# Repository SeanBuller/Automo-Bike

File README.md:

## Automo-Bike

Automatic bicycle gear changer (transmission). Fourth year design project (Capstone) for ECE (Electrical & Computer Engineering) at University of Waterloo.

## Synopsis

Controls 2 stepper motors based on external inputs from hall-effect sensor, and IMU (inertial measurement unit). 12 V battery input with 5 V regulator for MCU. 

The design is intended to be paired with the following stepper motors: 17HS13-0404S-PG27 and SY20STH30-0604A.

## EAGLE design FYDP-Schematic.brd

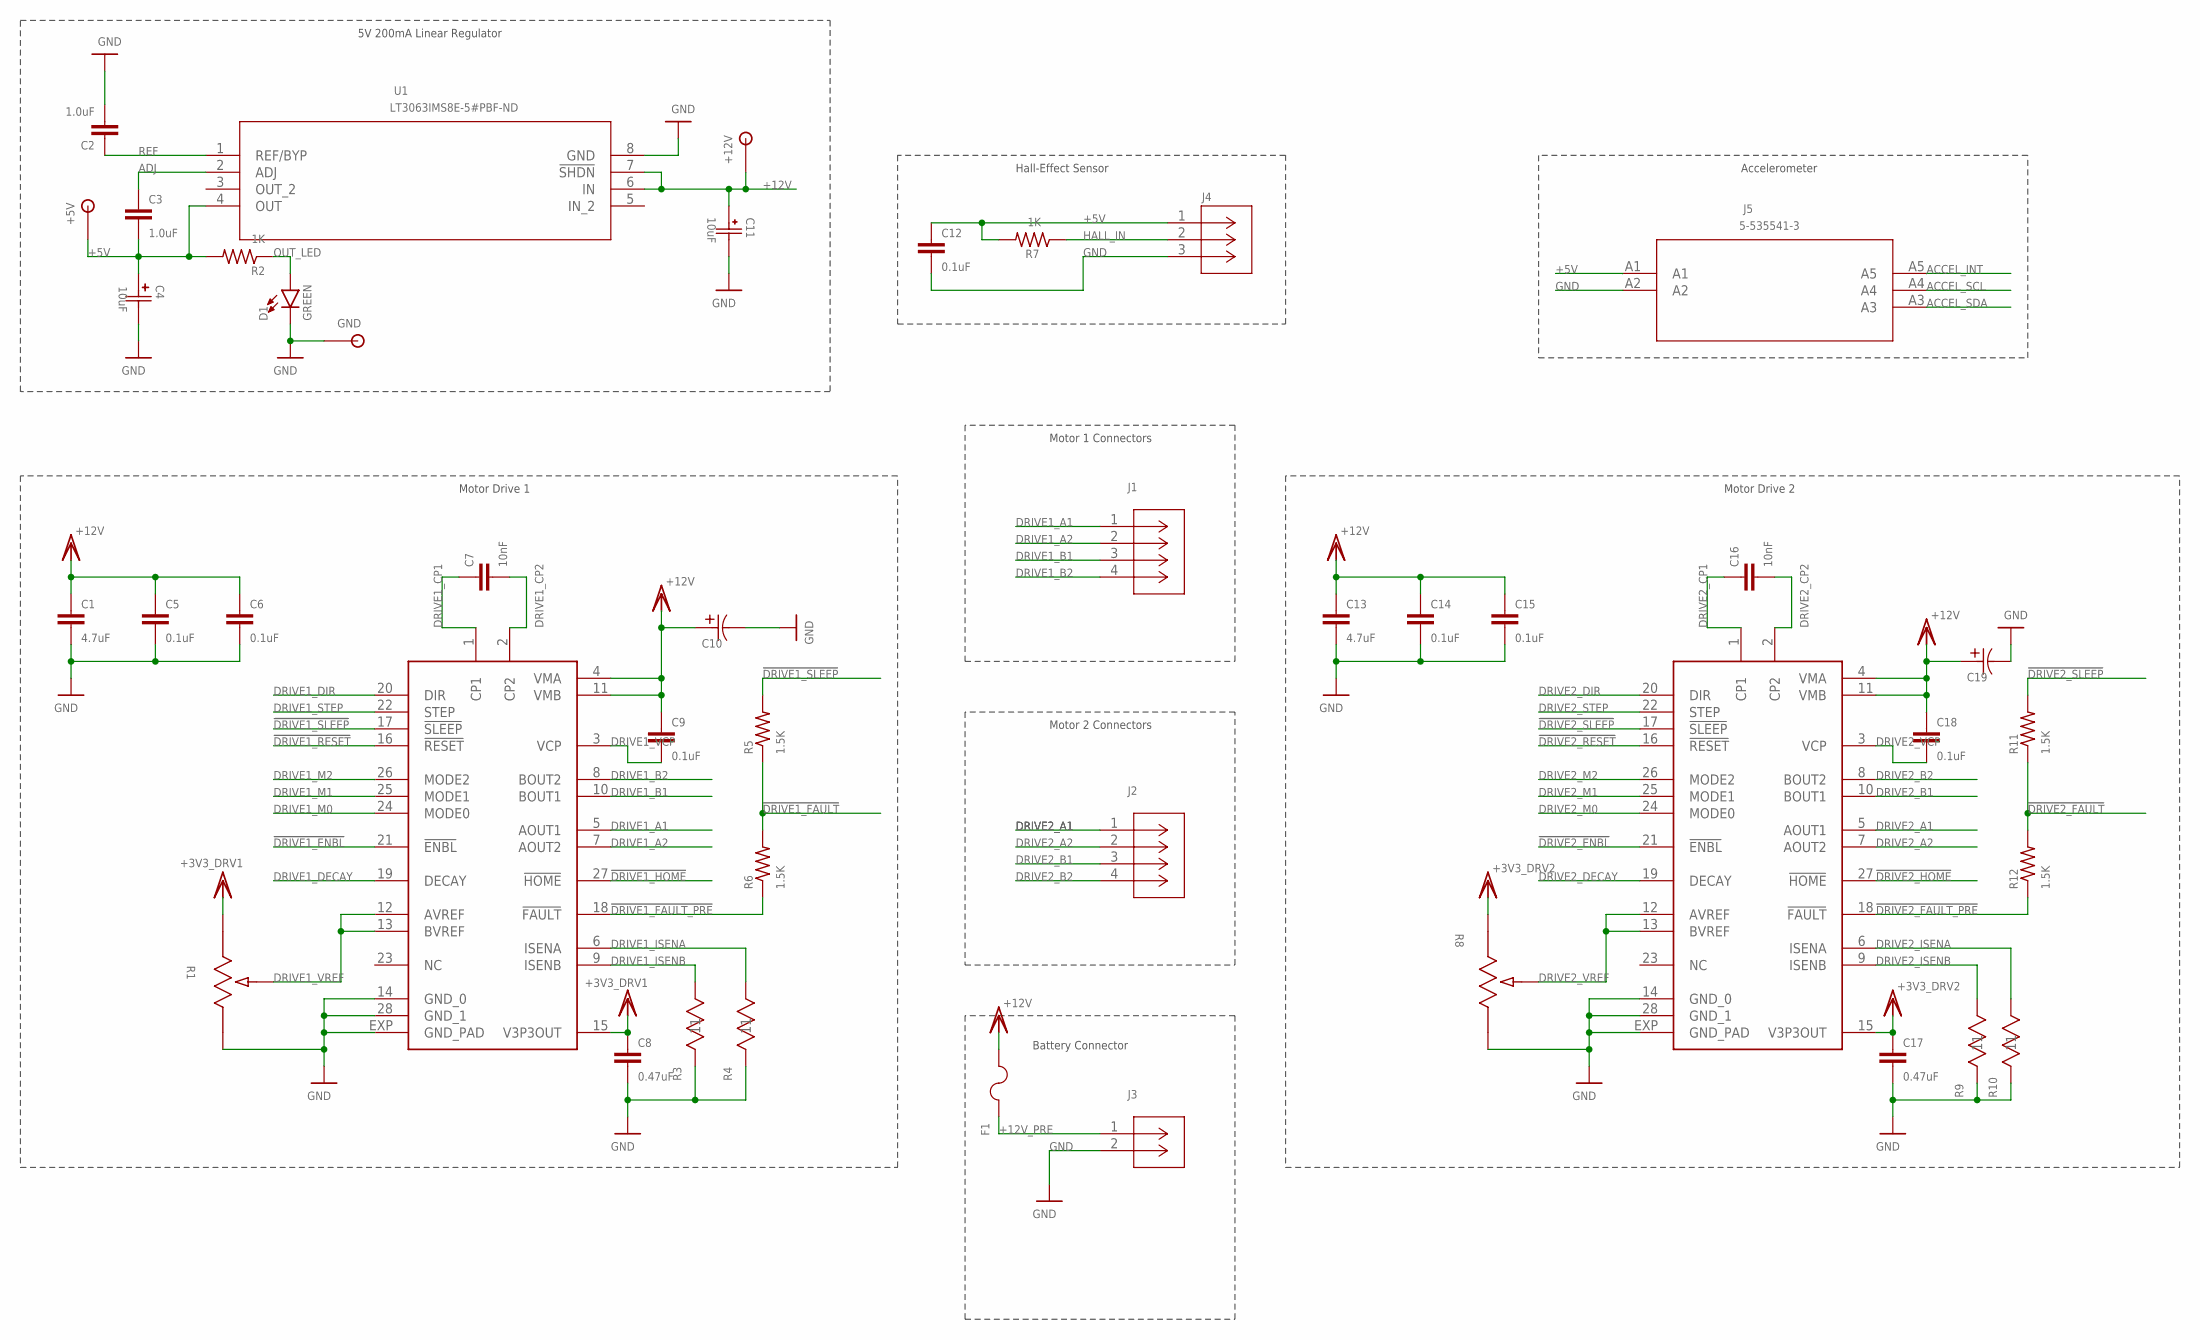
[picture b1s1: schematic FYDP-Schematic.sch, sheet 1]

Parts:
+5V, +12V: TESTPOINT
C1, C13: 4.7uF; 0603
C2, C3: 1.0uF; 0603
C4: 10uF; F93-C
C5, C6, C9, C12, C14, C15, C18: 0.1uF; 0603
C7, C16: 10nF; 0603
C8, C17: 0.47uF; 0603
C10, C19: UWX1C101MCL1GB; PCAP_6.3X5.4-ELECT
C11: 10uF; G-188
D1: GREEN; LED-0603
F1: 1210L110/12WR; 1210LSERIES
GND: TESTPOINT
J1, J2: 2029030-4; CONN_2029030-4
J3: 2029030-2; CONN_2029030-2
J4: 2029030-3; CONN_2029030-3
J5: 5-535541-3
R1, R8: 3314G-1-103E; POT_3314G
R2, R7: 1K; 0603
R3, R4, R9, R10: CSR1206FKR200; STA_CSR1206
R5, R6, R11, R12: 1.5K; 0603
U1: LT3063IMS8E-5#PBF-ND; MSOP-8_MS
U2, U3: DRV8825PWP; TSSOP-28

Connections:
!DRIVE1_ENBL!: U3.21 (!ENBL!); also elsewhere on the board
!DRIVE1_FAULT!: R5.1, R6.2; also elsewhere on the board
!DRIVE1_FAULT_PRE!: R6.1, U3.18 (!FAULT!)
!DRIVE1_HOME!: U3.27 (!HOME!); also elsewhere on the board
!DRIVE1_RESET!: U3.16 (!RESET!); also elsewhere on the board
!DRIVE1_SLEEP!: R5.2, U3.17 (!SLEEP!); also elsewhere on the board
!DRIVE2_ENBL!: U2.21 (!ENBL!); also elsewhere on the board
!DRIVE2_FAULT!: R11.1, R12.2; also elsewhere on the board
!DRIVE2_FAULT_PRE!: R12.1, U2.18 (!FAULT!)
!DRIVE2_HOME!: U2.27 (!HOME!); also elsewhere on the board
!DRIVE2_RESET!: U2.16 (!RESET!); also elsewhere on the board
!DRIVE2_SLEEP!: R11.2, U2.17 (!SLEEP!); also elsewhere on the board
+3V3_DRV1: C8.1, R1.1, U3.15 (V3P3OUT)
+3V3_DRV2: C17.1, R8.1, U2.15 (V3P3OUT)
+5V: +5V.TP, C3.2, C4.POS (1), C12.1, J4.1, J5.A1, R2.2, R7.2, U1.4 (OUT); also elsewhere on the board
+12V: +12V.TP, C1.1, C5.1, C6.1, C9.1, C10.1 (11), C11.PWR, C13.1, C14.1, C15.1, C18.1, C19.1 (11), F1.2, U1.6 (IN), U1.7 (!SHDN), U2.4 (VMA), U2.11 (VMB), U3.4 (VMA), U3.11 (VMB)
+12V_PRE: F1.1, J3.1
ACCEL_INT: J5.A5; also elsewhere on the board
ACCEL_SCL: J5.A4; also elsewhere on the board
ACCEL_SDA: J5.A3; also elsewhere on the board
ADJ: C3.1, U1.2 (ADJ)
DRIVE1_A1: J1.1, U3.5 (AOUT1)
DRIVE1_A2: J1.2, U3.7 (AOUT2)
DRIVE1_B1: J1.3, U3.10 (BOUT1)
DRIVE1_B2: J1.4, U3.8 (BOUT2)
DRIVE1_CP1: C7.1, U3.1 (CP1)
DRIVE1_CP2: C7.2, U3.2 (CP2)
DRIVE1_DECAY: U3.19 (DECAY); also elsewhere on the board
DRIVE1_DIR: U3.20 (DIR); also elsewhere on the board
DRIVE1_ISENA: R4.2 (22), U3.6 (ISENA)
DRIVE1_ISENB: R3.2 (22), U3.9 (ISENB)
DRIVE1_M0: U3.24 (MODE0); also elsewhere on the board
DRIVE1_M1: U3.25 (MODE1); also elsewhere on the board
DRIVE1_M2: U3.26 (MODE2); also elsewhere on the board
DRIVE1_STEP: U3.22 (STEP); also elsewhere on the board
DRIVE1_VCP: C9.2, U3.3 (VCP)
DRIVE1_VREF: R1.2, U3.12 (AVREF), U3.13 (BVREF)
DRIVE2_A1: J2.1, U2.5 (AOUT1)
DRIVE2_A2: J2.2, U2.7 (AOUT2)
DRIVE2_B1: J2.3, U2.10 (BOUT1)
DRIVE2_B2: J2.4, U2.8 (BOUT2)
DRIVE2_CP1: C16.1, U2.1 (CP1)
DRIVE2_CP2: C16.2, U2.2 (CP2)
DRIVE2_DECAY: U2.19 (DECAY); also elsewhere on the board
DRIVE2_DIR: U2.20 (DIR); also elsewhere on the board
DRIVE2_ISENA: R10.2 (22), U2.6 (ISENA)
DRIVE2_ISENB: R9.2 (22), U2.9 (ISENB)
DRIVE2_M0: U2.24 (MODE0); also elsewhere on the board
DRIVE2_M1: U2.25 (MODE1); also elsewhere on the board
DRIVE2_M2: U2.26 (MODE2); also elsewhere on the board
DRIVE2_STEP: U2.22 (STEP); also elsewhere on the board
DRIVE2_VCP: C18.2, U2.3 (VCP)
DRIVE2_VREF: R8.2, U2.12 (AVREF), U2.13 (BVREF)
GND: C1.2, C2.2, C4.GND (2), C5.2, C6.2, C8.2, C10.2 (22), C11.GND, C12.2, C13.2, C14.2, C15.2, C17.2, C19.2 (22), D1.C, GND.TP, J3.2, J4.3, J5.A2, R1.3, R3.1 (11), R4.1 (11), R8.3, R9.1 (11), R10.1 (11), U1.8 (GND), U2.14 (GND_0), U2.28 (GND_1), U2.EXP (GND_PAD), U3.14 (GND_0), U3.28 (GND_1), U3.EXP (GND_PAD); also elsewhere on the board
HALL_IN: J4.2, R7.1; also elsewhere on the board
OUT_LED: D1.A, R2.1
REF: C2.1, U1.1 (REF/BYP)

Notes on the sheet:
Motor 1 Connectors
Battery Connector
Motor 2 Connectors
5V 200mA Linear Regulator
Motor Drive 1
Motor Drive 2
Hall-Effect Sensor
Accelerometer

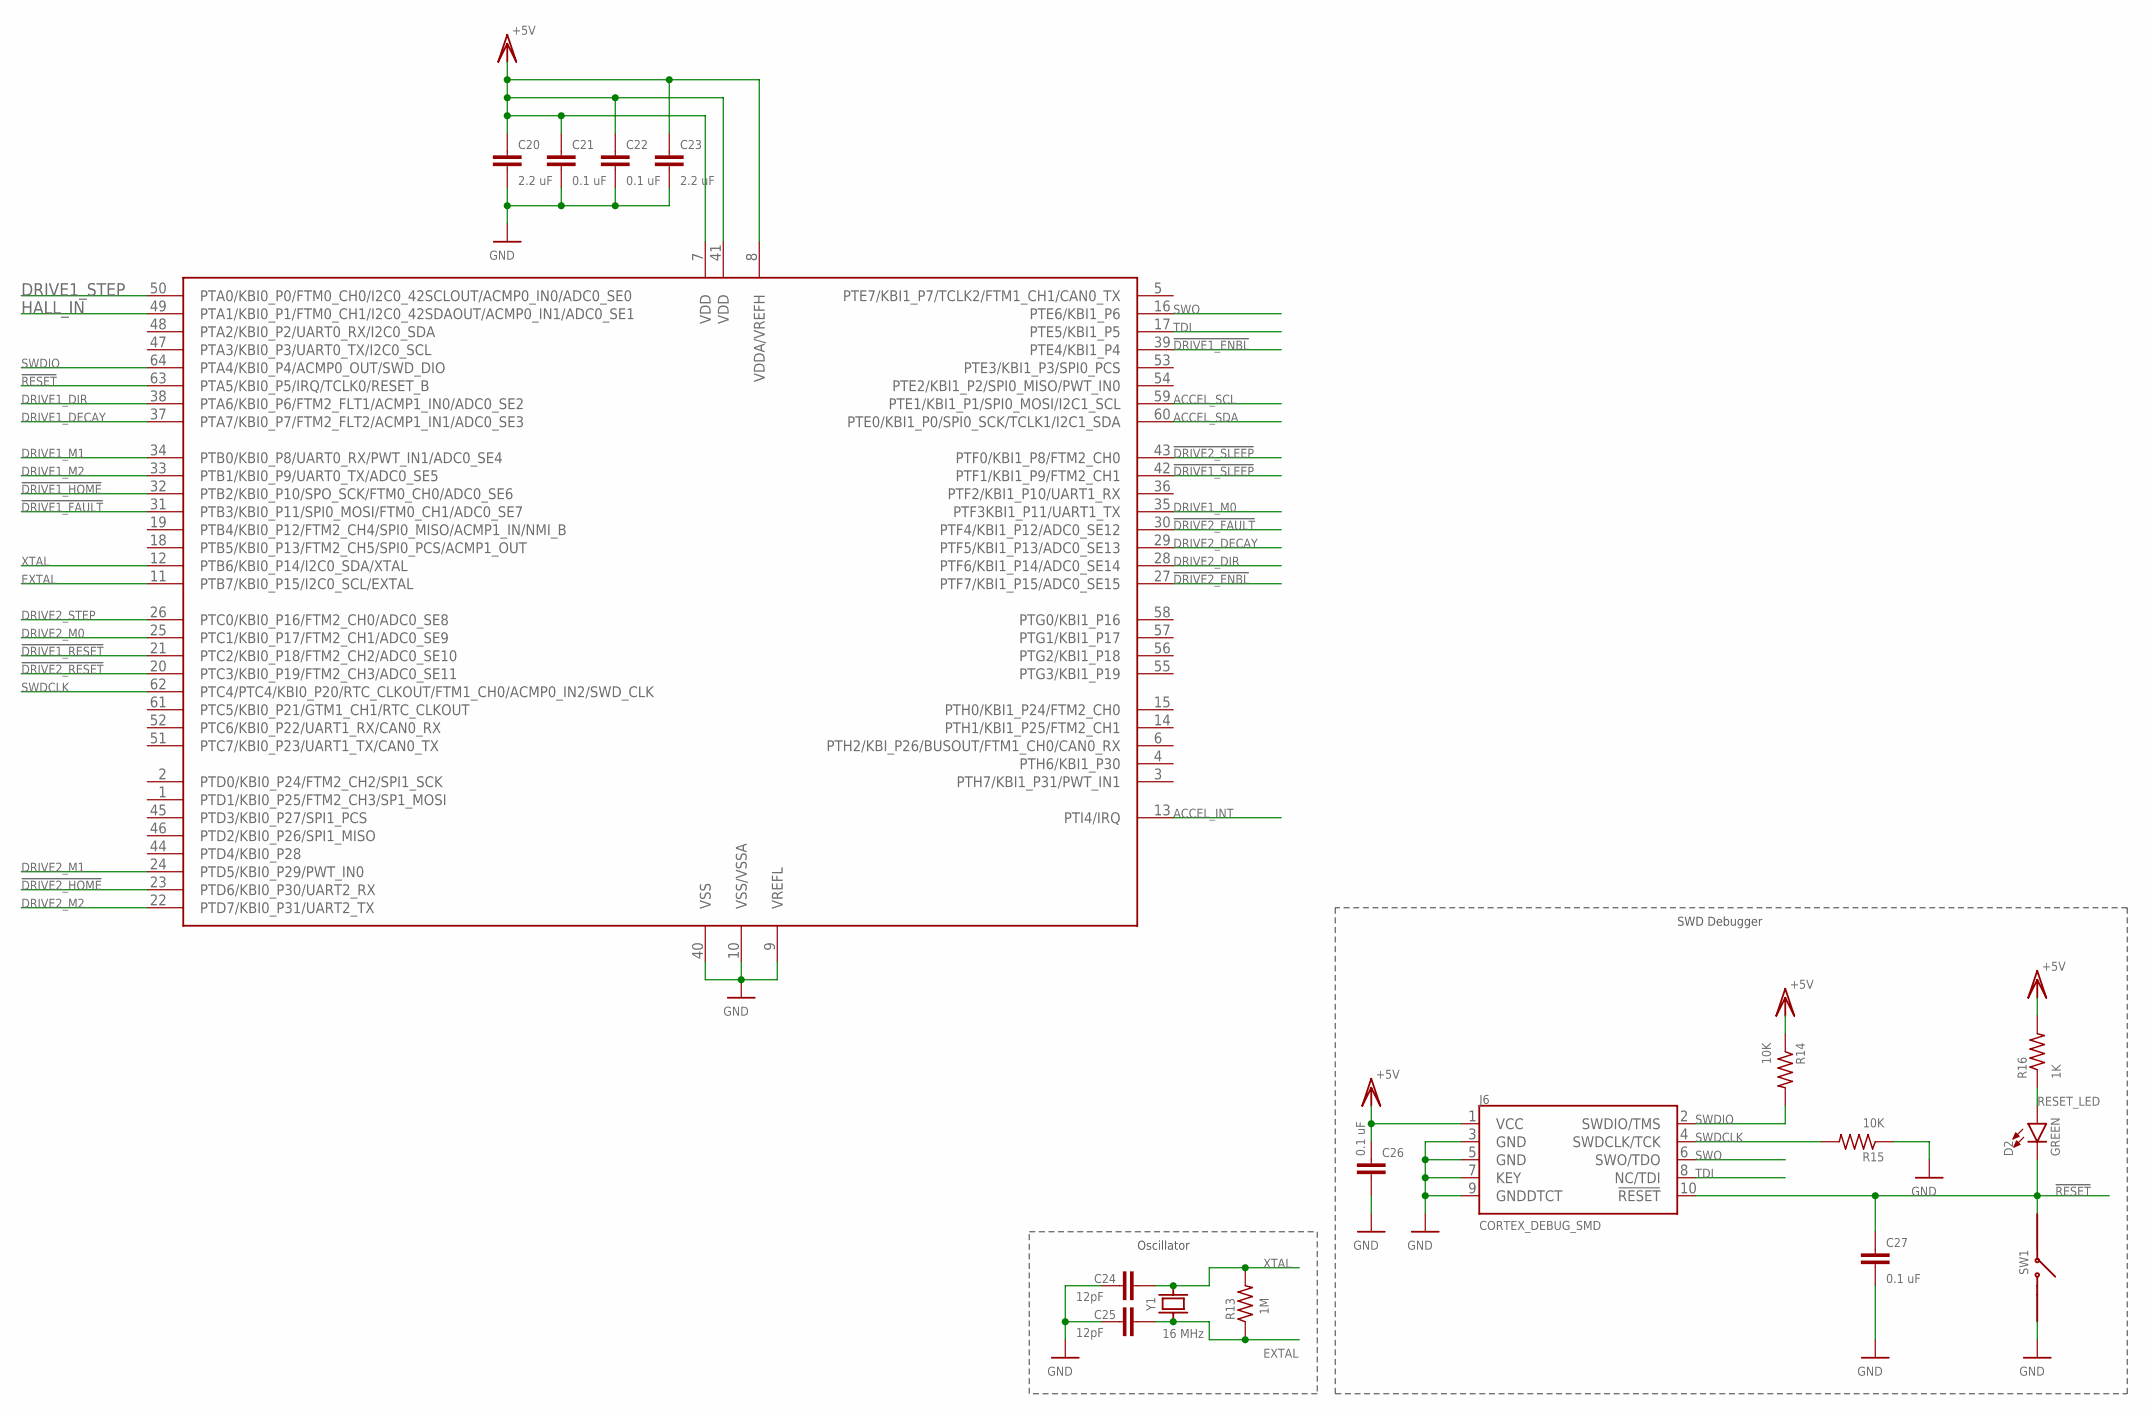
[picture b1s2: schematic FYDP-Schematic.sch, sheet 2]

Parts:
C20, C23: 2.2 uF; 0603
C21, C22, C26, C27: 0.1 uF; 0603
C24, C25: 12pF; 0603
D2: GREEN; LED-0603
J6: CORTEX_DEBUG_SMD; SAMTECH_FTSH-105-01
R13: 1M; 0603
R14, R15: 10K; 0603
R16: 1K; 0603
SW1: KSR223GNCLFG
U4: S9KEA128
Y1: 16 MHz; AT-16.000MAGE-T

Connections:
!DRIVE1_ENBL!: U4.39 (PTE4/KBI1_P4); also elsewhere on the board
!DRIVE1_FAULT!: U4.31 (PTB3/KBI0_P11/SPI0_MOSI/FTM0_CH1/ADC0_S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); also elsewhere on the board
!DRIVE1_HOME!: U4.32 (PTB2/KBI0_P10/SPO_SCK/FTM0_CH0/ADC0_SE6); also elsewhere on the board
!DRIVE1_RESET!: U4.21 (PTC2/KBI0_P18/FTM2_CH2/ADC0_SE10); also elsewhere on the board
!DRIVE1_SLEEP!: U4.42 (PTF1/KBI1_P9/FTM2_CH1); also elsewhere on the board
!DRIVE2_ENBL!: U4.27 (PTF7/KBI1_P15/ADC0_SE15); also elsewhere on the board
!DRIVE2_FAULT!: U4.30 (PTF4/KBI1_P12/ADC0_SE12); also elsewhere on the board
!DRIVE2_HOME!: U4.23 (PTD6/KBI0_P30/UART2_RX); also elsewhere on the board
!DRIVE2_RESET!: U4.20 (PTC3/KBI0_P19/FTM2_CH3/ADC0_SE11); also elsewhere on the board
!DRIVE2_SLEEP!: U4.43 (PTF0/KBI1_P8/FTM2_CH0); also elsewhere on the board
!RESET!: C27.1, D2.C, J6.10 (!RESET), SW1.1, U4.63 (PTA5/KBI0_P5/IRQ/TCLK0/RESET_B)
+5V: C20.1, C21.1, C22.1, C23.1, C26.1, J6.1 (VCC), R14.1, R16.2, U4.7 (VDD), U4.8 (VDDA/VREFH), U4.41 (VDD); also elsewhere on the board
ACCEL_INT: U4.13 (PTI4/IRQ); also elsewhere on the board
ACCEL_SCL: U4.59 (PTE1/KBI1_P1/SPI0_MOSI/I2C1_SCL); also elsewhere on the board
ACCEL_SDA: U4.60 (PTE0/KBI1_P0/SPI0_SCK/TCLK1/I2C1_SDA); also elsewhere on the board
DRIVE1_DECAY: U4.37 (PTA7/KBI0_P7/FTM2_FLT2/ACMP1_IN1/ADC0_S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); also elsewhere on the board
DRIVE1_DIR: U4.38 (PTA6/KBI0_P6/FTM2_FLT1/ACMP1_IN0/ADC0_S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); also elsewhere on the board
DRIVE1_M0: U4.35 (PTF3KBI1_P11/UART1_TX); also elsewhere on the board
DRIVE1_M1: U4.34 (PTB0/KBI0_P8/UART0_RX/PWT_IN1/ADC0_SE4); also elsewhere on the board
DRIVE1_M2: U4.33 (PTB1/KBI0_P9/UART0_TX/ADC0_SE5); also elsewhere on the board
DRIVE1_STEP: U4.50 (PTA0/KBI0_P0/FTM0_CH0/I2C0_42SCLOUT/ACM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); also elsewhere on the board
DRIVE2_DECAY: U4.29 (PTF5/KBI1_P13/ADC0_SE13); also elsewhere on the board
DRIVE2_DIR: U4.28 (PTF6/KBI1_P14/ADC0_SE14); also elsewhere on the board
DRIVE2_M0: U4.25 (PTC1/KBI0_P17/FTM2_CH1/ADC0_SE9); also elsewhere on the board
DRIVE2_M1: U4.24 (PTD5/KBI0_P29/PWT_IN0); also elsewhere on the board
DRIVE2_M2: U4.22 (PTD7/KBI0_P31/UART2_TX); also elsewhere on the board
DRIVE2_STEP: U4.26 (PTC0/KBI0_P16/FTM2_CH0/ADC0_SE8); also elsewhere on the board
EXTAL: C25.1, R13.1, U4.11 (PTB7/KBI0_P15/I2C0_SCL/EXTAL), Y1.1
GND: C20.2, C21.2, C22.2, C23.2, C24.2, C25.2, C26.2, C27.2, J6.3 (GND), J6.5 (GND), J6.7 (KEY), J6.9 (GNDDTCT), R15.1, SW1.2, U4.9 (VREFL), U4.10 (VSS/VSSA), U4.40 (VSS); also elsewhere on the board
HALL_IN: U4.49 (PTA1/KBI0_P1/FTM0_CH1/I2C0_42SDAOUT/ACM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); also elsewhere on the board
RESET_LED: D2.A, R16.1
SWDCLK: J6.4 (SWDCLK/TCK), R15.2, U4.62 (PTC4/PTC4/KBI0_P20/RTC_CLKOUT/FTM1_CH0/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)
SWDIO: J6.2 (SWDIO/TMS), R14.2, U4.64 (PTA4/KBI0_P4/ACMP0_OUT/SWD_DIO)
SWO: J6.6 (SWO/TDO), U4.16 (PTE6/KBI1_P6)
TDI: J6.8 (NC/TDI), U4.17 (PTE5/KBI1_P5)
XTAL: C24.1, R13.2, U4.12 (PTB6/KBI0_P14/I2C0_SDA/XTAL), Y1.2

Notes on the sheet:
SWD Debugger
Oscillator

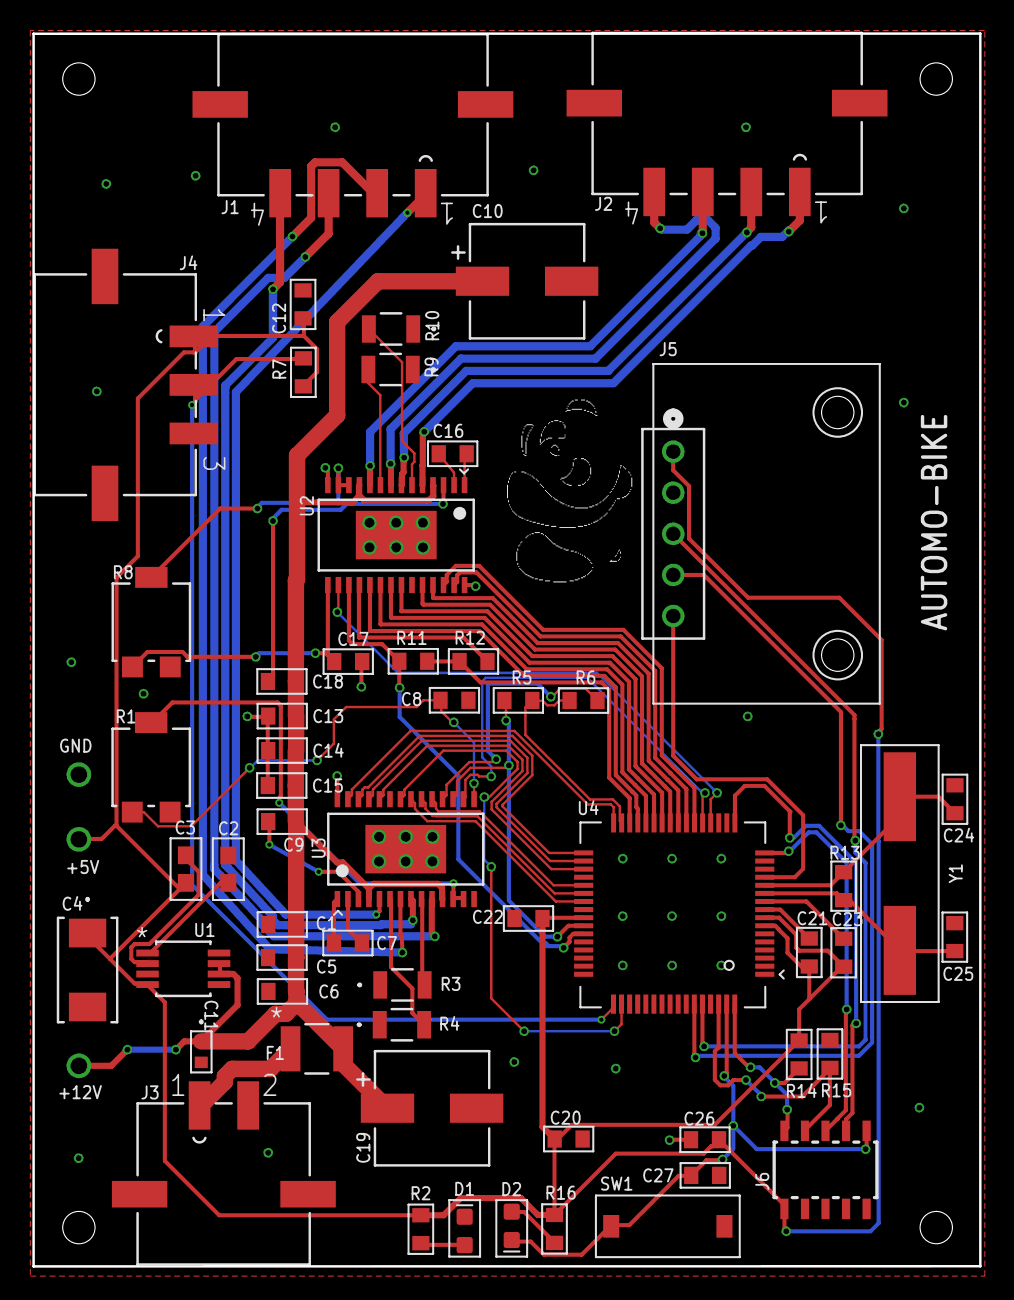
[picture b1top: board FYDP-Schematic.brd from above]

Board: 2 copper layers, 58.5 x 76.2 mm, 61 parts (0 on the bottom side), 65 nets.

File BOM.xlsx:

Qty | Value | Device | Package | Parts | Digikey Part # | Unit Price | Per Board Price
11 | 0.1 uF | C_0603 | 603 | C21, C22, C26, C27, C5, C6, C9, C12, C14, C15, C18 | 399-6856-1-ND | 0.13 | 0.82
2 | 0.47uF | C_0603 | 603 | C8, C17 | 490-3295-1-ND | 0.23 | 0.46
2 | 1.0uF | 1.0UF-0603-16V-10% | 603 | C2, C3 | 587-1251-1-ND | 0.13 | 0.26
4 | 1.5K | R_0603 | 603 | R5, R6, R11, R12 | RNCP0603FTD1K50CT-ND | 0.14 | 0.5600000000000001
2 | 10K | R_0603 | 603 | R14, R15 | RR08P10.0KDCT-ND | 0.16 | 0.32
2 | 10nF | C_0603 | 603 | C7, C16 | 399-1091-1-ND | 0.13 | 0.26
1 | 10uF | F931C106MBA | F93-C | C4 | 478-8238-1-ND | 0.68 | 0.68
1 | 10uF | GRM188C81C106MA73D | G-188 | C11 | 490-7198-1-ND | 0.51 | 0.51
1 | 1210L110/12WR | 1210L110/12WR | 1210LSERIES | F1 | F6132CT-ND | 1.33 | 1.33
2 | 12pF | C_0603 | 603 | C24, C25 | 1276-1254-1-ND | 0.13 | 0.26
1 | 16 MHz | AT-16.000MAGE-T | AT-16.000MAGE-T | Y1 | 887-1608-1-ND | 0.9399999999999999 | 0.9399999999999999
3 | 1K | R_0603 | 603 | R2, R7, R16 | RR08P1.0KDCT-ND | 0.16 | 0.48
1 | 1M | R_0603 | 603 | R13 | A119955CT-ND | 0.74 | 0.74
2 | 2.2 uF | C_0603 | 603 | C20, C23 | 587-1430-1-ND | 0.16 | 0.32
1 | 2029030-2 | 2029030-2 | CONN_2029030-2 | J3 | A99181CT-ND | 1.21 | 1.21
1 | 2029030-3 | 2029030-3 | CONN_2029030-3 | J4 | A99182CT-ND | 1.27 | 1.27
2 | 2029030-4 | 2029030-4 | CONN_2029030-4 | J1, J2 | A99183CT-ND | 1.37 | 2.74
2 | 3314G-1-103E | 3314G-1-103E | POT_3314G | R1, R8 | 3314G-103ECT-ND | 3.1 | 6.2
2 | 4.7uF | C_0603 | 603 | C1, C13 | 1276-2087-1-ND | 0.19 | 0.38
1 | 5-535541-3 | 5-535541-3 | 5-535541-3 | J5 | A32919-ND | 1.95 | 1.95
1 | CORTEX_DEBUG_SMD | CORTEX_DEBUG_SMD | SAMTECH_FTSH-105-01 | J6 | SAM8799-ND | 4.18 | 4.18
4 | CSR1206FKR200 | CSR1206FKR200 | STA_CSR1206 | R3, R4, R9, R10 | CSR1206FKR200CT-ND | 0.64 | 2.56
2 | DRV8825PWP | DRV8825PWP | TSSOP-28 | U2, U3 | 296-28915-5-ND | 6.36 | 12.72
1 | RED | LED-RED0603 | LED-0603 | D2 | 160-1447-1-ND | 0.39 | 0.39
1 | GREEN | LED-GREEN0603 | LED-0603 | D1 | 160-1446-1-ND | 0.39 | 0.39
1 | KSR223GNCLFG | KSR223GNCLFG | KSR223GNCLFG | SW1 | 401-1704-1-ND | 1.86 | 1.86
1 | LT3063IMS8E-5#PBF-ND | LT3063IMS8EPBF | MSOP-8_MS | U1 | LT3063IMS8E-5#PBF-ND | 5.57 | 5.57
1 | S9KEA128 | S9KEA128 | S9KEA128 | U4 | S9KEAZ128AMLH-ND | 5.23 | 5.23
1 | TESTPOINT | TESTPOINT | TESTPOINT | GND | 36-5001-ND | 0.53 | 0.53
2 | TESTPOINT | TESTPOINT | TESTPOINT | +5V, +12V | 36-5000-ND | 0.53 | 1.06
2 | UWX1C101MCL1GB | UWX1C101MCL1GB | PCAP_6.3X5.4-ELECT | C10, C19 | 493-2105-1-ND | 0.44 | 0.88
2 | 2029047-4 |  |  |  | A99177-ND | 0.75 | 1.5
1 | 2029047-3 |  |  |  | A99176-ND | 0.65 | 0.65
1 | 2029047-2 |  |  |  | A99175-ND | 0.5600000000000001 | 0.5600000000000001
 |  |  |  |  |  | TOTAL | 59.77000000000001

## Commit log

2019-01-03 Add README

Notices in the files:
parts and their libraries:
SparkFun-Capacitors: Licensing: Creative Commons ShareAlike 4.0 International - https://creativecommons.org/licenses/by-sa/4.0
